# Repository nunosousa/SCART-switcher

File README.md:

# SCART switcher

A work-in-progress hardware design for switching SCART video and audio. The repository contains KiCad schematics and PCB layouts for the main switcher and a separate power-supply board, along with fabrication exports and mechanical CAD models.

> **Status:** The repository does not document prototype bring-up, measured performance, or production readiness. Treat the design and existing fabrication files as work in progress; review and validate them before ordering boards or connecting equipment.

## Design overview

The schematics and board layout describe:

- Six SCART inputs and one SCART output.
- Analog video/RGB and stereo audio input and output stages.
- Priority-based input selection using SCART input-active/function signaling.
- RCA left/right audio outputs.
- A separate power-supply board, intended to keep power-circuit changes from requiring a respin of the larger switcher board.
- A “silent input” path in the main schematic, implemented as a dummy audio/video input.

The separate supply schematic describes a 12 V DC input, a 5 V rail rated for up to 300 mA, a 9 V rail rated for up to 100 mA, and a 12 V fan connection. Check the schematic and the exact assembly requirements before selecting a supply or fan.

## Repository contents

| Path | Contents |
| --- | --- |
| [`ECAD/SCART_switcher/`](ECAD/SCART_switcher/) | Main KiCad project, schematics, PCB, BOM, PDFs, renders, STEP model, and Gerber/drill exports |
| [`ECAD/Power_supply/`](ECAD/Power_supply/) | Separate power-supply KiCad project and its corresponding design and fabrication files |
| [`CAD/`](CAD/) | FreeCAD assembly, SCART connector models, standoffs, and heatsink models |
| [`ECAD/README.md`](ECAD/README.md) | Note on why the power circuitry is on a separate board |

Custom footprints and symbols are kept alongside the ECAD projects. Keep the included library tables and custom library folders available when opening the projects in KiCad.

## Viewing and editing

Open the relevant `.kicad_pro` file in KiCad:

- Main switcher: [`SCART_switcher.kicad_pro`](ECAD/SCART_switcher/SCART_switcher.kicad_pro)
- Power supply: [`Power_supply.kicad_pro`](ECAD/Power_supply/Power_supply.kicad_pro)

The corresponding `.kicad_sch` and `.kicad_pcb` files are the editable schematic and board sources. PDFs are convenient for browsing, while the top/bottom images and STEP files provide visual and 3D references.

## Board previews

### Main switcher

### Power supply

## Existing design outputs

Both projects include BOM CSVs, schematic PDFs, 3D board models, and zipped Gerber/drill packages:

- [Main switcher BOM](ECAD/SCART_switcher/SCART_switcher-BOM.csv) · [schematic PDF](ECAD/SCART_switcher/SCART_switcher.pdf) · [Gerbers ZIP](ECAD/SCART_switcher/Gerbers/SCART_switcher.zip)
- [Power-supply BOM](ECAD/Power_supply/Power_supply-BOM.csv) · [schematic PDF](ECAD/Power_supply/Power_supply.pdf) · [Gerbers ZIP](ECAD/Power_supply/Gerbers/Power_supply.zip)

These are checked-in outputs, not a guarantee that they match the latest editable design. Regenerate them from the reviewed project revision before fabrication.

## Before fabrication or use

Suggested next steps:

1. Run KiCad electrical-rule checks and PCB design-rule checks on both projects; review and resolve or document exceptions.
2. Verify that generated Gerbers, drill files, BOMs, and assembly data correspond to the final schematic and PCB revisions.
3. Confirm component availability, substitutions, connector pinouts, mechanical clearances, and the intended enclosure. The CAD folder contains component and assembly models, but the repository does not describe a finalized enclosure.
4. Bench-test the supply rails and thermal behavior, then test switching, video levels/termination, audio performance, and SCART control signaling with suitable equipment.
5. Add measured results, known limitations, operating instructions, and build/assembly guidance here once they are established.

No electrical, thermal, signal-quality, or compatibility measurements are claimed by this README.

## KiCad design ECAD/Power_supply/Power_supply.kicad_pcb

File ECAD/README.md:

This folder contains de PCB projects for the main PCB switcher board and for a separate power supply.

Due to the size of the main switcher board, I decided to make the power circuitry in a separate board so that if there is any issue with it, I don't have to roll a new (and expensive) whole PCB with everything.

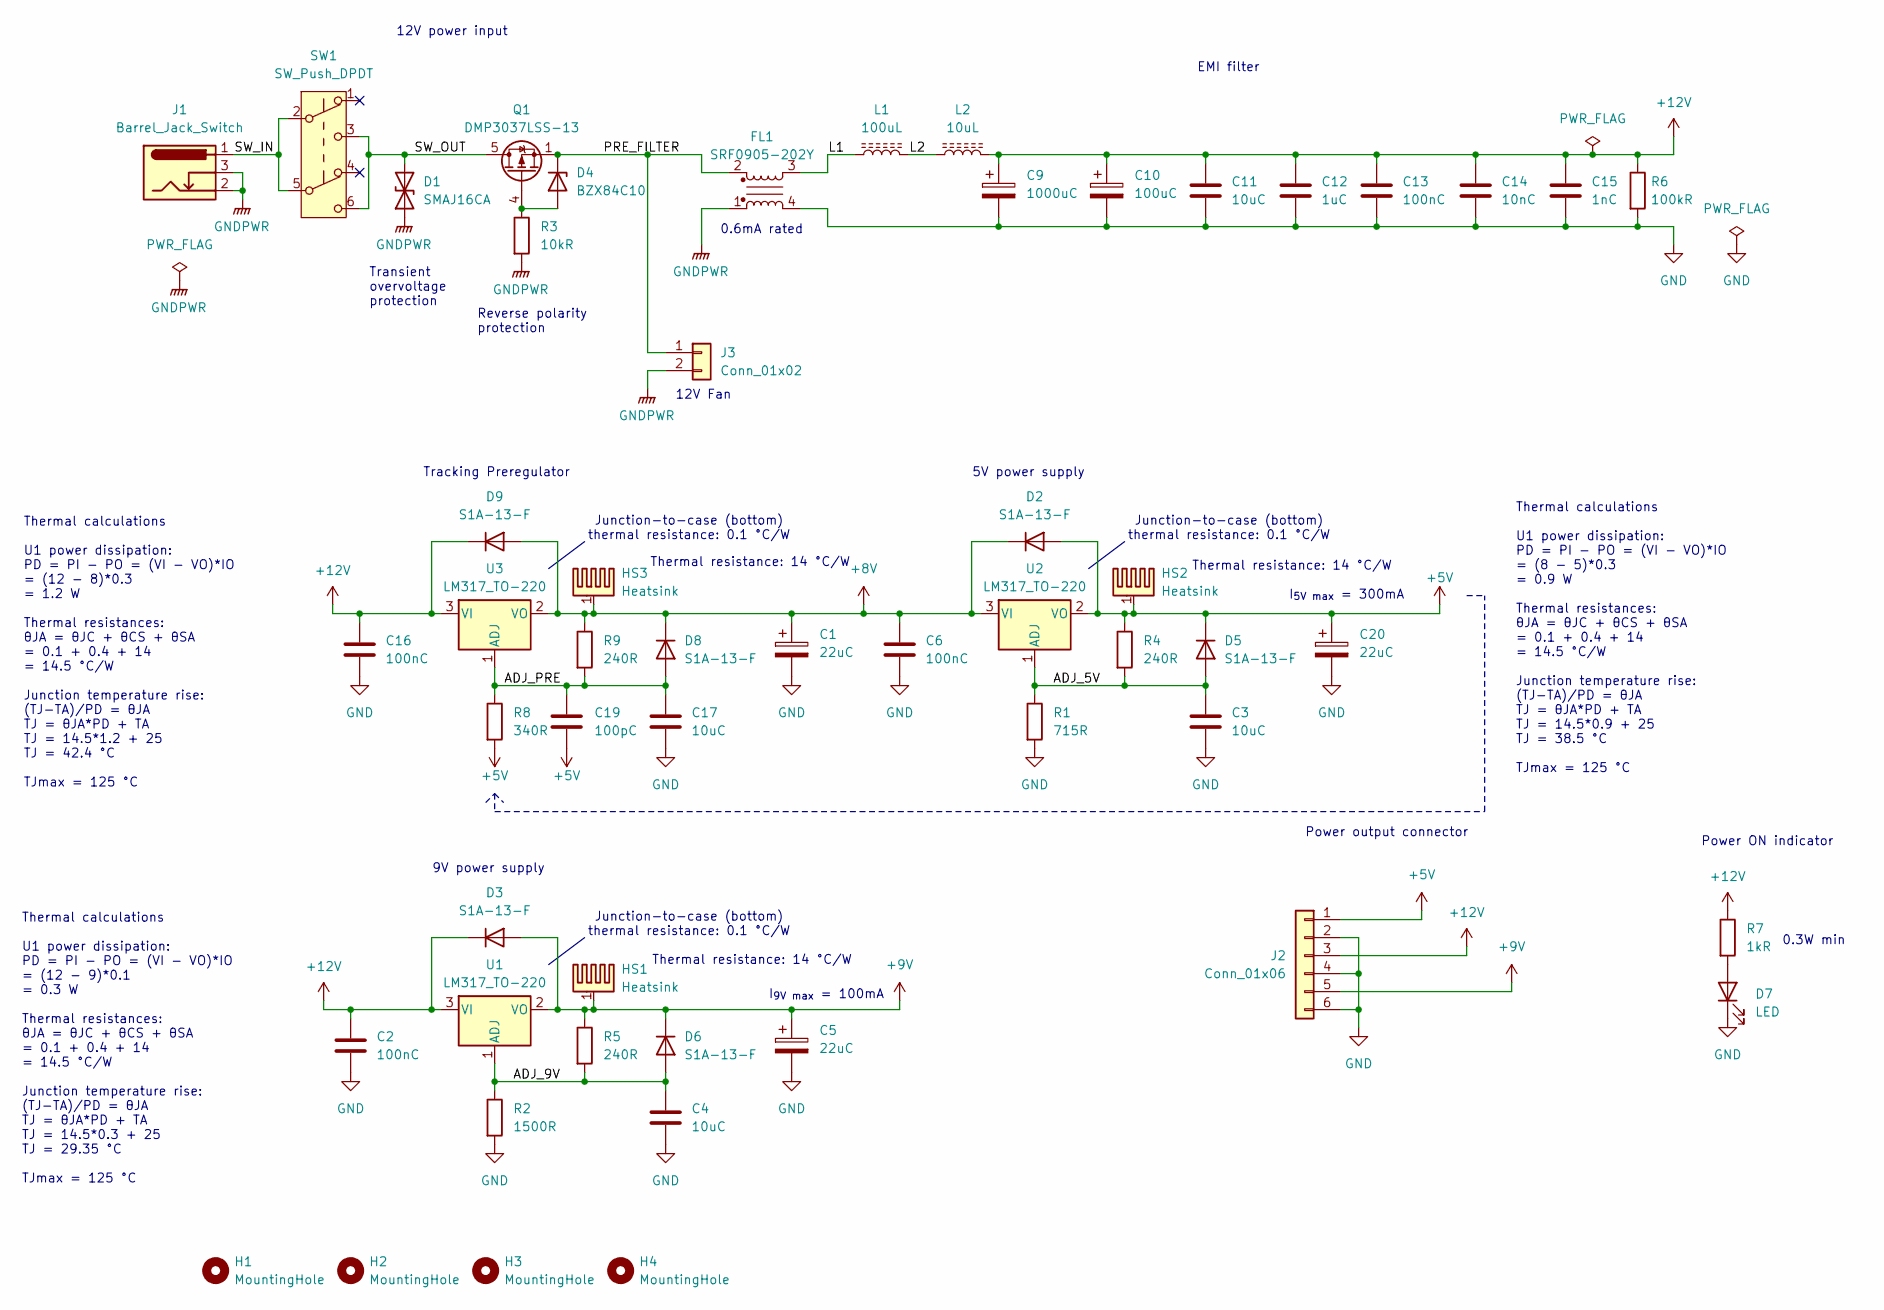
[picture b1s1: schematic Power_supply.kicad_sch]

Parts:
C1, C5, C20: 22uC; CP_Elec_5x5.4; MPN UWT1C220MCL1GB
C2, C6, C13, C16: 100nC; C_1206_3216Metric; MPN CC1206KRX7R9BB104
C3, C4, C11, C17: 10uC; C_1206_3216Metric; MPN CL31A106KBHNNNE
C9: 1000uC; CP_Elec_10x10.5; MPN EEEFT1E102UP
C10: 100uC; CP_Elec_8x10; MPN UWT1H101MNL1GS
C12: 1uC; C_1206_3216Metric; MPN CL31B105KBHNNNE
C14: 10nC; C_1206_3216Metric; MPN CC1206KKX7RCBB103
C15: 1nC; C_1206_3216Metric; MPN CC1206KKX7RDBB102
C19: 100pC; C_0805_2012Metric; MPN CL21C101JBANNNC
D1: SMAJ16CA; D_SMA; MPN SMAJ16CA-13-F
D2, D3, D5, D6, D8, D9: S1A-13-F; D_SMA; MPN S1A-13-F
D4: BZX84C10; SOT-23; MPN BZX84C10-7-F
D7: LED; LED_D5.0mm; MPN 333-2SURD/S530-A3
FL1: SRF0905-202Y; Filter_Bourns_SRF0905_6.0x9.2mm; MPN SRF0905-202Y
H1, H2, H3, H4: MountingHole; MountingHole_3.2mm_M3
HS1, HS2, HS3: Heatsink; Heatsink_Fischer_SK104-STC-STIC_35x13mm_2xDrill2.5mm
J1: Barrel_Jack_Switch; BarrelJack_Horizontal; MPN DC-005-20A
J2: Conn_01x06; PinSocket_1x06_P2.54mm_Vertical
J3: Conn_01x02; JST_XH_B2B-XH-A_1x02_P2.50mm_Vertical
L1: 100uL; L_Taiyo-Yuden_NR-80xx; MPN NRS8040T101MJGK
L2: 10uL; L_Taiyo-Yuden_NR-30xx; MPN NR3015T100M
Q1: DMP3037LSS-13; SOIC-8_3.9x4.9mm_P1.27mm; MPN DMP3037LSS-13
R1: 715R; R_0805_2012Metric; MPN PTFR0805B715RP9
R2: 1500R; R_0805_2012Metric; MPN RC0805FR-071K5L
R3: 10kR; R_0805_2012Metric; MPN AC0805FR-0710KL
R4, R5, R9: 240R; R_0805_2012Metric; MPN RC0805FR-07240RL
R6: 100kR; R_1210_3225Metric; MPN RC0805FR-07100KL
R7: 1kR; R_1210_3225Metric; MPN 1210W2F1001T5E
R8: 340R; R_0805_2012Metric; MPN ARG05BTC3400
SW1: SW_Push_DPDT; PN22SJNA03QE; MPN PS-22E05
U1, U2, U3: LM317_TO-220; TO-220-3_Vertical; MPN LM317KCS

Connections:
+5V: C19.2, C20.1, D2.2 (A), D5.1 (K), HS2.1, J2.1, R4.1, R8.2, U2.2 (VO)
+8V: C1.1, C6.1, D2.1 (K), D8.1 (K), D9.2 (A), HS3.1, R9.1, U2.3 (VI), U3.2 (VO)
+9V: C5.1, D3.2 (A), D6.1 (K), HS1.1, J2.5, R5.1, U1.2 (VO)
+12V: C2.1, C9.1, C10.1, C11.1, C12.1, C13.1, C14.1, C15.1, C16.1, D3.1 (K), D9.1 (K), J2.3, L2.2, R6.1, R7.1, U1.3 (VI), U3.3 (VI)
/ADJ_5V: C3.1, D5.2 (A), R1.1, R4.2, U2.1 (ADJ)
/ADJ_9V: C4.1, D6.2 (A), R2.1, R5.2, U1.1 (ADJ)
/ADJ_PRE: C17.1, C19.1, D8.2 (A), R8.1, R9.2, U3.1 (ADJ)
/L1: FL1.3, L1.1
/L2: L1.2, L2.1
/PRE_FILTER: D4.3 (K), FL1.2, J3.1, Q1.1 (S), Q1.2 (S), Q1.3 (S)
/SW_IN: J1.1, SW1.2 (B), SW1.5 (B)
/SW_OUT: D1.2 (A2), Q1.5 (D), Q1.6 (D), Q1.7 (D), Q1.8 (D), SW1.3 (C), SW1.6 (C)
GND: C1.2, C2.2, C3.2, C4.2, C5.2, C6.2, C9.2, C10.2, C11.2, C12.2, C13.2, C14.2, C15.2, C16.2, C17.2, C20.2, D7.1 (K), FL1.4, J2.2, J2.4, J2.6, R1.2, R2.2, R6.2
GNDPWR: D1.1 (A1), FL1.1, J1.2, J1.3, J3.2, R3.2
unnamed: D4.1 (A), Q1.4 (G), R3.1
unnamed: D7.2 (A), R7.2

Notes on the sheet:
Thermal resistance: 14 °C/W
12V power input
I_{5V max} = 300mA
5V power supply
Power ON indicator
12V Fan
Power output connector
I_{9V max} = 100mA
Junction-to-case (bottom) thermal resistance: 0.1 °C/W
Reverse polarity protection
0.6mA rated
0.3W min
EMI filter
Thermal calculations U1 power dissipation: PD = PI - PO = (VI - VO)*IO = (12 - 9)*0.1 = 0.3 W Thermal resistances: θJA = θJC + θCS + θSA = 0.1 + 0.4 + 14 = 14.5 °C/W Junction temperature rise: (TJ-TA)/PD = θJA TJ = θJA*PD + TA TJ = 14.5*0.3 + 25 TJ = 29.35 °C TJmax = 125 °C
Thermal calculations U1 power dissipation: PD = PI - PO = (VI - VO)*IO = (8 - 5)*0.3 = 0.9 W Thermal resistances: θJA = θJC + θCS + θSA = 0.1 + 0.4 + 14 = 14.5 °C/W Junction temperature rise: (TJ-TA)/PD = θJA TJ = θJA*PD + TA TJ = 14.5*0.9 + 25 TJ = 38.5 °C TJmax = 125 °C
9V power supply
Tracking Preregulator
Thermal calculations U1 power dissipation: PD = PI - PO = (VI - VO)*IO = (12 - 8)*0.3 = 1.2 W Thermal resistances: θJA = θJC + θCS + θSA = 0.1 + 0.4 + 14 = 14.5 °C/W Junction temperature rise: (TJ-TA)/PD = θJA TJ = θJA*PD + TA TJ = 14.5*1.2 + 25 TJ = 42.4 °C TJmax = 125 °C
Transient overvoltage protection

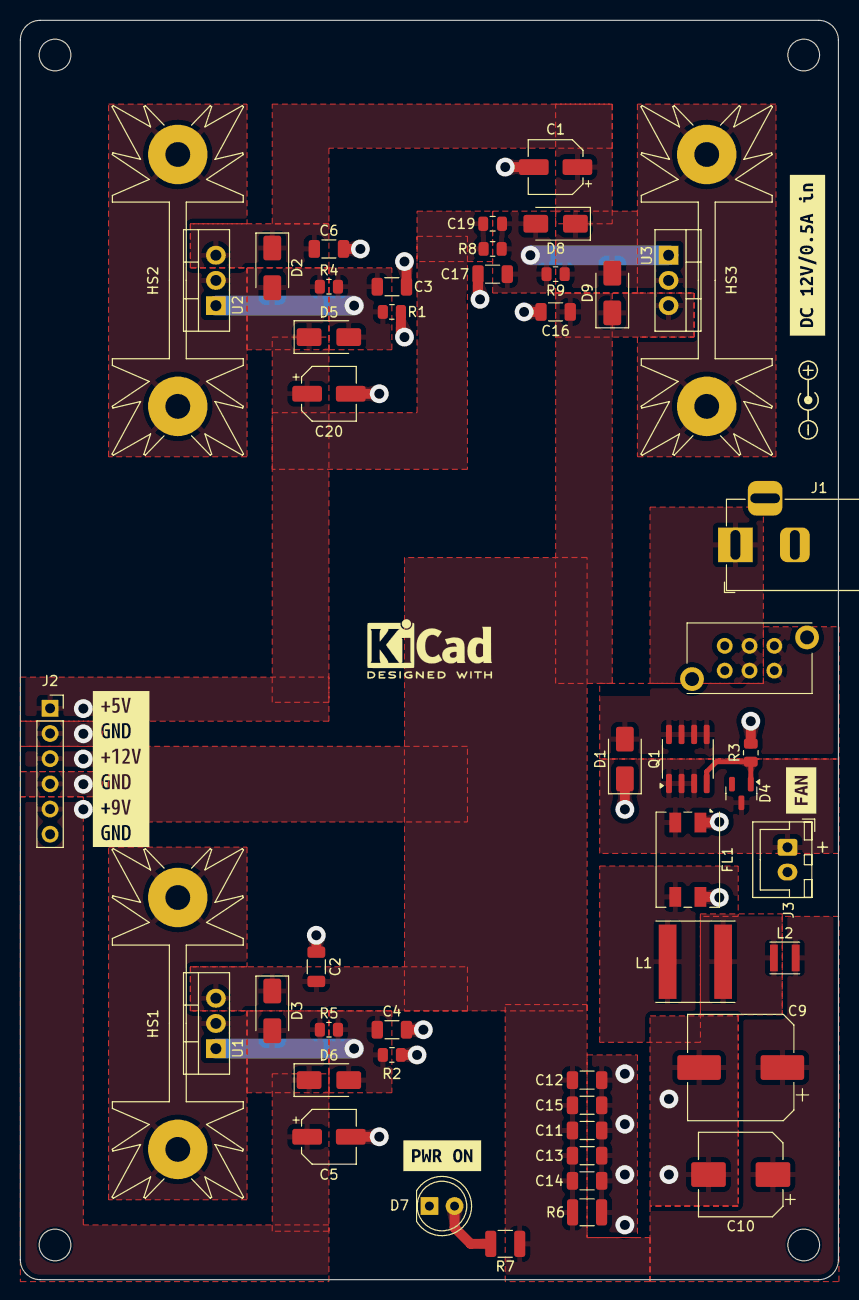
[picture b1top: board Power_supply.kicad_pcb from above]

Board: 2 copper layers, 82.5 x 127.0 mm, 57 parts (0 on the bottom side), 16 nets.

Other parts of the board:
kibuzzard-67A3D3AE: G***; kibuzzard-67A3D3AE
kibuzzard-67B25D9F: G***; kibuzzard-67B25D9F
kibuzzard-67B5004D: G***; kibuzzard-67B5004D
kibuzzard-67B50421: G***; kibuzzard-67B50421

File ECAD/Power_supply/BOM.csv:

"Reference","Value","Datasheet","Footprint","Qty","DNP","MPN","Status"
"C1,C5,C20","22uC","https://www.lcsc.com/datasheet/lcsc_datasheet_2409291036_Nic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","Capacitor_SMD:CP_Elec_5x5.4","3","","UWT1C220MCL1GB","OK"
"C2,C6,C13,C16","100nC","https://datasheet.lcsc.com/lcsc/2304140030_YAGEO-CC1206KRX7R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","Capacitor_SMD:C_1206_3216Metric","4","","CC1206KRX7R9BB104","OK"
"C3,C4,C11,C17","10uC","https://datasheet.lcsc.com/lcsc/2304140030_Samsung-Electro-M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","Capacitor_SMD:C_1206_3216Metric","4","","CL31A106KBHNNNE","OK"
"C9","1000uC","https://datasheet.lcsc.com/lcsc/1912111437_PANASONIC-EEEFT1E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","Capacitor_SMD:CP_Elec_10x10.5","1","","EEEFT1E102UP","OK"
"C10","100uC","https://datasheet.lcsc.com/lcsc/2304140030_Nichicon-UWT1H101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","Capacitor_SMD:CP_Elec_8x10","1","","UWT1H101MNL1GS","OK"
"C12","1uC","https://www.lcsc.com/datasheet/lcsc_datasheet_2304140030_Sam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","Capacitor_SMD:C_1206_3216Metric","1","","CL31B105KBHNNNE","OK"
"C14","10nC","https://datasheet.lcsc.com/lcsc/2304140030_YAGEO-CC1206KKX7R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","Capacitor_SMD:C_1206_3216Metric","1","","CC1206KKX7RCBB103","OK"
"C15","1nC","https://datasheet.lcsc.com/lcsc/2304140030_YAGEO-CC1206KKX7R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","Capacitor_SMD:C_1206_3216Metric","1","","CC1206KKX7RDBB102","OK"
"C19","100pC","https://www.lcsc.com/datasheet/lcsc_datasheet_2304140030_Sam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","Capacitor_SMD:C_0805_2012Metric","1","","CL21C101JBANNNC","OK"
"D1","SMAJ16CA","https://datasheet.lcsc.com/lcsc/1809192020_Diodes-Incorporat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","Diode_SMD:D_SMA","1","","SMAJ16CA-13-F","OK"
"D2,D3,D5,D6,D8,D9","S1A-13-F","https://datasheet.lcsc.com/lcsc/2304140030_Diodes-Incorporat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","Diode_SMD:D_SMA","6","","S1A-13-F","OK"
"D4","BZX84C10","https://datasheet.lcsc.com/lcsc/2304140030_Diodes-Incorporat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","Package_TO_SOT_SMD:SOT-23","1","","BZX84C10-7-F","OK"
"D7","LED","https://datasheet.lcsc.com/lcsc/1810271709_Everlight-Elec-33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","LED_THT:LED_D5.0mm","1","","333-2SURD/S530-A3","OK"
"FL1","SRF0905-202Y","https://datasheet.lcsc.com/lcsc/2304140030_BOURNS-SRF0905-20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","Filter:Filter_Bourns_SRF0905_6.0x9.2mm","1","","SRF0905-202Y","OK"
"HS1,HS2,HS3","Heatsink","~","Heatsink_custom:Heatsink_Fischer_SK104-STC-STIC_35x13mm_2xDrill2.5mm","3","","",""
"J1","Barrel_Jack_Switch","https://datasheet.lcsc.com/lcsc/2108131730_Korean-Hroparts-E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","Connector_BarrelJack:BarrelJack_Horizontal","1","","DC-005-20A","OK"
"J2","Conn_01x06","https://datasheet.lcsc.com/lcsc/2306091006_HCTL-PZ254-1-06-W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","Connector_PinSocket_2.54mm:PinSocket_1x06_P2.54mm_Vertical","1","","",""
"J3","Conn_01x02","~","Connector_JST:JST_XH_B2B-XH-A_1x02_P2.50mm_Vertical","1","","",""
"L1","100uL","https://www.lcsc.com/datasheet/lcsc_datasheet_2410121518_Tai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","Inductor_SMD:L_Taiyo-Yuden_NR-80xx","1","","NRS8040T101MJGK","OK"
"L2","10uL","https://datasheet.lcsc.com/lcsc/2304140030_Taiyo-Yuden-NR301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","Inductor_SMD:L_Taiyo-Yuden_NR-30xx","1","","NR3015T100M","OK"
"Q1","DMP3037LSS-13","https://datasheet.lcsc.com/lcsc/1805251754_Diodes-Incorporat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","Package_SO:SOIC-8_3.9x4.9mm_P1.27mm","1","","DMP3037LSS-13","OK"
"R1","715R","https://www.lcsc.com/datasheet/lcsc_datasheet_2409280130_RES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","Resistor_SMD:R_0805_2012Metric","1","","PTFR0805B715RP9","OK"
"R2","1500R","https://datasheet.lcsc.com/lcsc/2304140030_YAGEO-RC0805FR-07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","Resistor_SMD:R_0805_2012Metric","1","","RC0805FR-071K5L","OK"
"R3","10kR","https://datasheet.lcsc.com/lcsc/2304140030_YAGEO-AC0805FR-07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","Resistor_SMD:R_0805_2012Metric","1","","AC0805FR-0710KL","OK"
"R4,R5,R9","240R","https://datasheet.lcsc.com/lcsc/2304140030_YAGEO-RC0805FR-07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","Resistor_SMD:R_0805_2012Metric","3","","RC0805FR-07240RL","OK"
"R6","100kR","https://datasheet.lcsc.com/lcsc/2304140030_YAGEO-RC0805FR-07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","Resistor_SMD:R_1210_3225Metric","1","","RC0805FR-07100KL","OK"
"R7","1kR","https://datasheet.lcsc.com/lcsc/2206010000_UNI-ROYAL-Uniroya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","Resistor_SMD:R_1210_3225Metric","1","","1210W2F1001T5E","OK"
"R8","340R","https://www.lcsc.com/datasheet/lcsc_datasheet_2410121212_Vik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","Resistor_SMD:R_0805_2012Metric","1","","ARG05BTC3400","OK"
"SW1","SW_Push_DPDT","https://datasheet.lcsc.com/lcsc/2108301530_G-Switch-PS-22E05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","Button_Switch_THT_custom:PN22SJNA03QE","1","","PS-22E05","OK"
"U1,U2,U3","LM317_TO-220","https://datasheet.lcsc.com/lcsc/2003172043_Texas-Instruments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","Package_TO_SOT_THT:TO-220-3_Vertical","3","","LM317KCS","OK"

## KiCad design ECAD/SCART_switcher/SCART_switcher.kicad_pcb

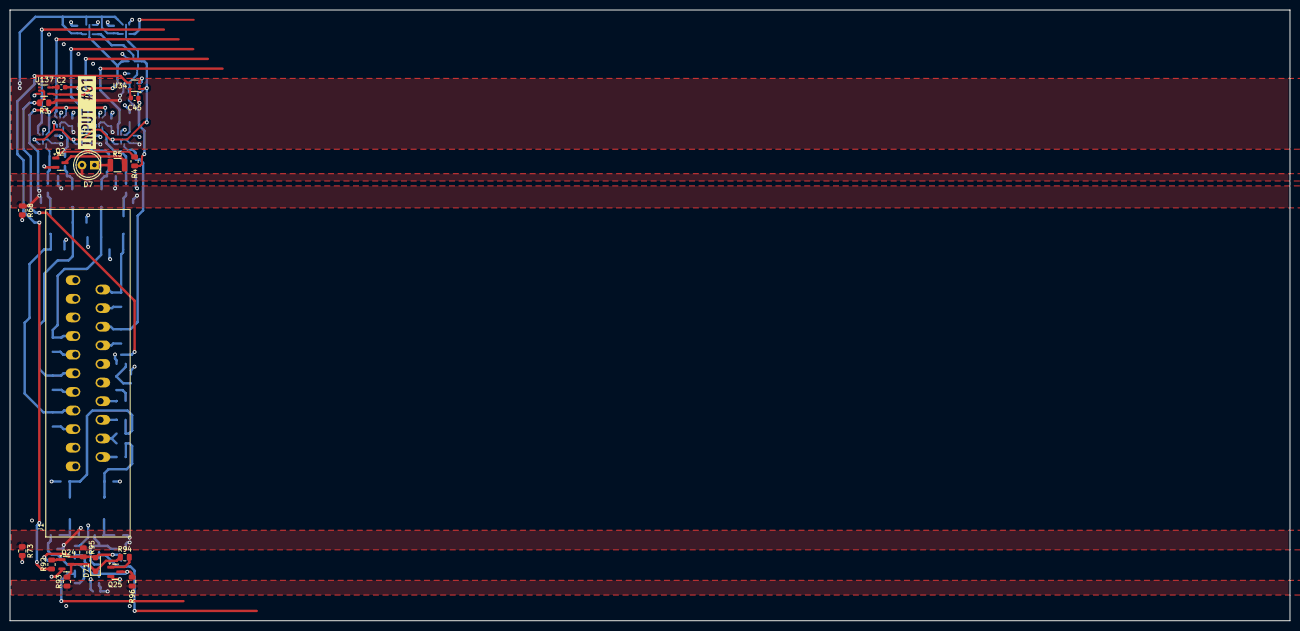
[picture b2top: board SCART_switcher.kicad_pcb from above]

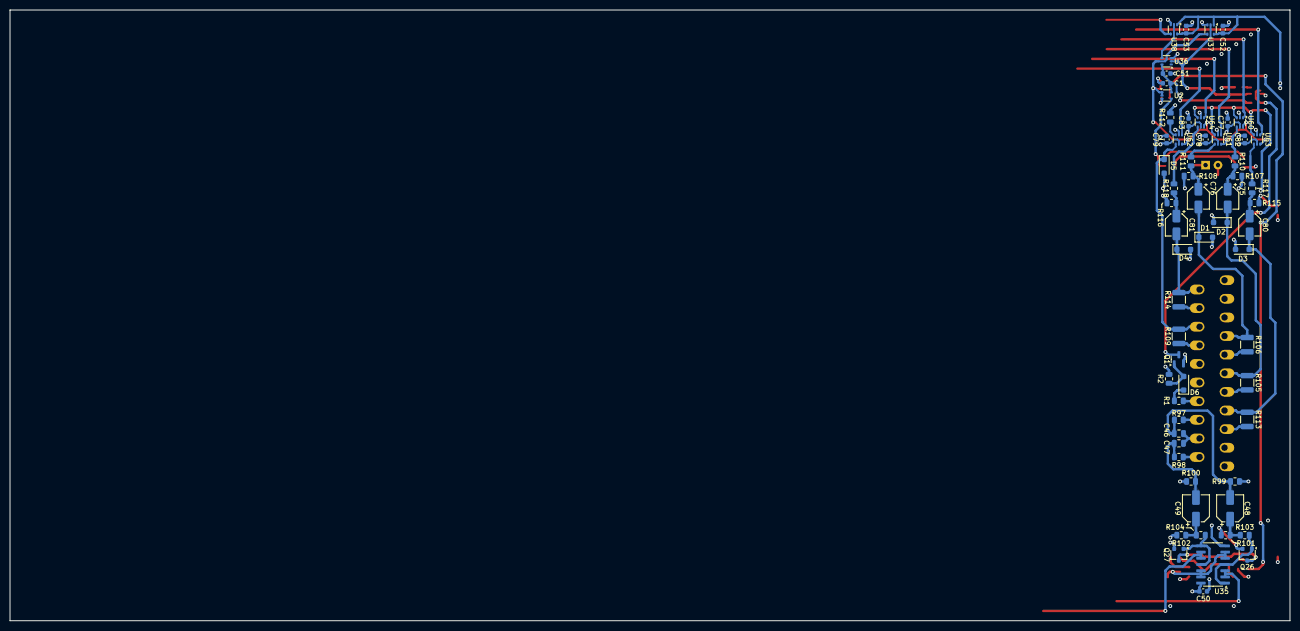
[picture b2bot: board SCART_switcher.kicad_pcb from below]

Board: 4 copper layers, 262.0 x 125.0 mm, 82 parts (61 on the bottom side), 46 nets.

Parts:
C1, C2, C45, C50, C51, C52, C53, C77, C78, C79, C82, C83: 100nC; C_0603_1608Metric
C46, C47: 1nC; C_0805_2012Metric
C48, C49: 22uC; CP_Elec_5x5.4
C75, C76, C80, C81: 47uC; CP_Elec_4x5.8
D1, D2, D3, D4, D5: BZT52H-B6V8; D_SOD-123F
D6: BZT52H-C3V3; D_SOD-123F
D7: LED; LED_D5.0mm
D71: BAS16H; D_SOD-123F
J1: SCART-F
Q1, Q2, Q24, Q25: BC847; SOT-23
Q26, Q27: 2SK209; SC-59
R1, R92, R94, R112: 10kR; R_0805_2012Metric
R2, R95, R99, R100: 220kR; R_0805_2012Metric
R3, R4, R93, R96: 4k7R; R_0805_2012Metric
R5: 1kR; R_1210_3225Metric
R68, R73, R110, R111, R117, R118: 1kR; R_0805_2012Metric
R97, R98: 100R; R_0805_2012Metric
R101, R102, R107, R108, R115, R116: 100kR; R_0805_2012Metric
R103, R104: 20kR; R_0805_2012Metric
R105, R106, R109, R113, R114: 75R; R_1210_3225Metric
U2, U34, U37, U38: 74LVC1G08; SOT-353_SC-70-5
U35: CD4066; SOIC-14_3.9x8.7mm_P1.27mm
U36: 74LVC1G04; SOT-353_SC-70-5
U60, U61, U62, U63, U64: 74LVC1G3157; SOT-363_SC-70-6
U137: 74LVC1G14; SOT-353_SC-70-5
kibuzzard-65C7DEEF: G***; kibuzzard-65C7DEEF

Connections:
+2V5: R68.1, R107.2, R108.2, R115.2, R116.2, U60.3, U61.3, U63.3, U64.3
+4V5: Q26.2 (S), Q27.2 (S), R73.1, R95.2, R101.2, R102.2
+5V: C1.1, C2.1, C45.1, C51.1, C52.1, C53.1, C77.1, C78.1, C79.1, C82.1, C83.1, R3.1, U2.5 (VCC), U34.5 (VCC), U36.5 (VCC), U37.1, U37.5 (VCC), U38.1, U38.5 (VCC), U60.5 (V+), U61.5 (V+), U62.5 (V+), U63.5 (V+), U64.5 (V+), U137.5 (VCC)
+9V: C50.1, R93.1, R96.1, U35.14 (V_{DD})
/AUDIO_LEFT: U35.2, U35.3
/AUDIO_RIGHT: U35.9, U35.10
/SCART input 1/AUDIO_LEFT_SCART_IN: J1.6, R97.1
/SCART input 1/AUDIO_RIGHT_SCART_IN: J1.2, R98.1
/SCART input 1/Audio input stage/AUDIO_OUT_ENABLE: Q25.3 (C), R96.2, U35.5, U35.6, U35.12, U35.13
/SCART input 1/Audio input stage/MUTE: D71.2 (A), Q26.3 (G), Q27.3 (G), R95.1
/SCART input 1/BLANKING_SCART_IN: D5.1 (K), J1.16, R109.1, U62.4
/SCART input 1/BLUE_SCART_IN: C80.2, D3.1 (K), J1.7, R113.1
/SCART input 1/FUNCTION_SCART_IN: J1.8, R1.1
/SCART input 1/GREEN_SCART_IN: C75.2, D2.1 (K), J1.11, R105.1
/SCART input 1/IN_ACTIVE: U36.2, U37.2, U137.4
/SCART input 1/IN_ENABLE: U2.1, U2.2, U34.1, U34.2, U37.4, U60.6, U61.6, U62.6, U63.6, U64.6
/SCART input 1/RED_SCART_IN: C76.2, D1.1 (K), J1.15, R106.1
/SCART input 1/VIDEO_RGB_SYNC_SCART_IN: C81.2, D4.1 (K), J1.20, R114.1
GND: C1.2, C2.2, C45.2, C46.2, C47.2, C50.2, C51.2, C52.2, C53.2, C77.2, C78.2, C79.2, C82.2, C83.2, D1.2 (A), D2.2 (A), D3.2 (A), D4.2 (A), D5.2 (A), J1.4, J1.5, J1.9, J1.13, J1.14, J1.18, J1.21, Q1.2 (E), Q2.2 (E), Q24.2 (E), Q25.2 (E), R2.2, R68.2, R73.2, R99.2, R100.2, R105.2, R106.2, R109.2, R112.2, R113.2, R114.2, U2.3 (GND), U34.3 (GND), U35.7 (V_{SS}), U36.3 (GND), U37.3 (GND), U38.3 (GND), U60.2 (GND), U61.2 (GND), U62.2 (GND), U63.2 (GND), U64.2 (GND), U137.3 (GND)
unnamed: C46.1, C48.2, R97.2, R99.1
unnamed: C47.1, C49.2, R98.2, R100.1
unnamed: C48.1, R101.1, R103.1
unnamed: C49.1, R102.1, R104.1
unnamed: C75.1, R107.1, R110.1
unnamed: C76.1, R108.1, R111.1
unnamed: C80.1, R115.1, R117.1
unnamed: C81.1, R116.1, R118.1
unnamed: D6.2 (A), Q1.1 (B), R2.1
unnamed: D6.1 (K), R1.2
unnamed: D7.1 (K), R5.1
unnamed: D71.1 (K), Q24.3 (C), R93.2, R94.1
unnamed: Q1.3 (C), R3.2, U137.2
unnamed: Q2.1 (B), R4.2
unnamed: Q2.3 (C), R5.2
unnamed: Q24.1 (B), R92.2
unnamed: Q25.1 (B), R94.2
unnamed: Q26.1 (D), R103.2, U35.1, U35.4
unnamed: Q27.1 (D), R104.2, U35.8, U35.11
unnamed: R4.1, U2.4
unnamed: R92.1, U34.4
unnamed: R110.2, U60.4
unnamed: R111.2, U61.4
unnamed: R112.1, U62.3
unnamed: R117.2, U63.4
unnamed: R118.2, U64.4
unnamed: U36.4, U38.2

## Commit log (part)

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2023-08-14 First commit.
2023-08-15 progressed cad
2023-08-16 progressed ECAD
2023-08-17 Progressed ECAD.
2023-08-18 progressed work
2023-08-25 Created circuit simulation.
2023-08-31 Circuit simplification
2023-09-07 Progressed simulations
2023-10-04 ECAD progress
2023-10-28 progresed ECAD
2023-12-02 Progressed CAD/ECAD.
2023-12-02 Progressed CAD.
2023-12-08 ERC fixes.
2023-12-10 Progressed ECAD. Error fixing and cleanup.
2023-12-22 Error fix.
2023-12-28 Added separate project for input only.
2024-01-14 Cleanup and new power supply pcb
2024-02-17 Replicated design.
2024-02-24 Updated to Kicad 8.
2024-02-25 KiCad 8 footprint cleanup
2024-11-20 Rename ECAD.md to README.md
2025-01-27 Removed 12V for LED indicator.
2025-01-27 Progressed PCB.
2025-01-28 Changed voltage reference.
2025-02-01 Updated PCB layout.
2025-02-01 Progressed PCB layout.
2025-02-02 Minor silkscreen fixes.
2025-02-02 DRC fixes.
2025-02-04 Fixed DRC errors.
2025-02-04 Completed PCB layout.
2025-02-05 Minor updates to PCB.
2025-02-05 Generated Gerber files.
2025-02-05 Generated images.
2025-02-07 Added mounting holes to PCB.
2025-02-07 Thermal calculations.
2025-02-08 Updated the schematic.
2025-02-12 Updated schematic
2025-02-16 Improved layout.
2025-02-16 Progressed PCB
2025-02-16 Added heatsink 3D model.
2025-02-18 Added Fan.
2025-02-19 Minor tweeks.
2025-02-22 BOM updates.
2025-02-22 BOM fixes.
2025-02-22 BOM fixes
2025-02-23 Updated output files.
2025-02-23 Fixes.
2025-02-24 Minor change.
2025-02-25 Fix alignment mistake.
2025-02-27 Minor alignment fix.
2025-02-27 CAD redo
2025-02-28 Updated CAD.
2025-03-01 Added Top cover.
